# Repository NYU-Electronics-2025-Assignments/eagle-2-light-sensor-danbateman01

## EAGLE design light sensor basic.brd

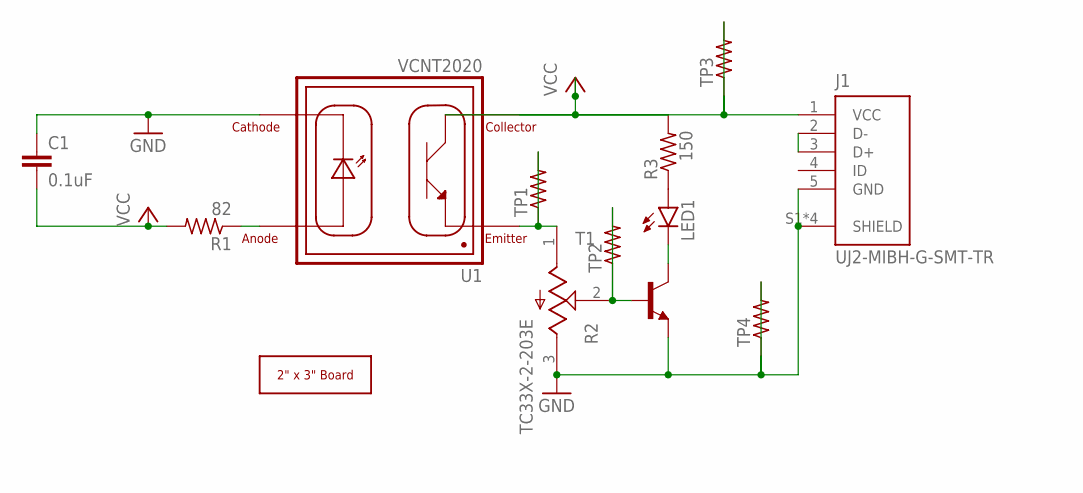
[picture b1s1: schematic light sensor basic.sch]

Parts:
C1: 0.1uF; C1206
J1: UJ2-MIBH-G-SMT-TR; CUI_UJ2-MIBH-G-SMT-TR
LED1: LEDSML0805; SML0805
R1: 82; R1206
R2: TC33X-2-203E; TRIM_TC33X-2-203E
R3: 150; R0805
T1: -NPN-SOT23-EBC; SOT23-EBC
TP1: R-US_R0805; R0805
TP2, TP3, TP4: R-US_R1206; R1206
U1: VCNT2020; XDCR_VCNT2020
U$1: 2X3_BOARD_V2

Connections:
GND: C1.1, J1.5 (GND), J1.S1 (SHIELD), J1.S2 (SHIELD), J1.S3 (SHIELD), J1.S4 (SHIELD), R2.3 (CW), T1.E, TP4.1, TP4.2, U1.4 (CATHODE)
unnamed: R1.1, U1.3 (ANODE)
unnamed: J1.2 (D-), J1.3 (D+)
unnamed: R2.2 (W), T1.B, TP2.1, TP2.2
unnamed: LED1.C, T1.C
unnamed: R2.1 (CCW), TP1.1, TP1.2, U1.1 (EMITTER)
unnamed: LED1.A, R3.1
VCC: C1.2, J1.1 (VCC), R1.2, R3.2, TP3.1, TP3.2, U1.2 (COLLECTOR)

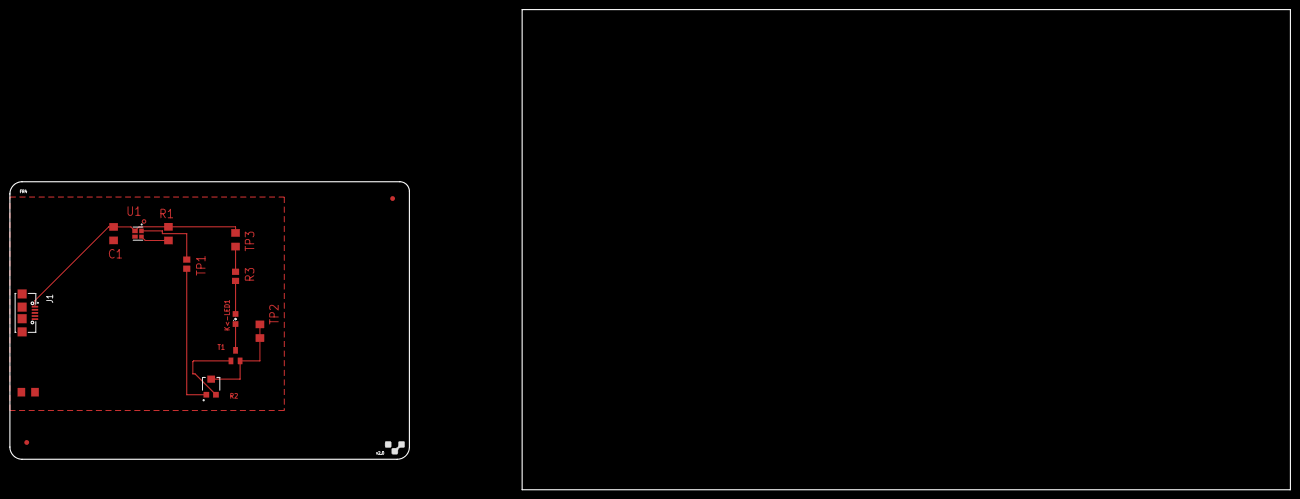
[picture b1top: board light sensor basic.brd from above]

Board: 2 copper layers, 83.2 x 57.8 mm, 13 parts (0 on the bottom side), 8 nets.

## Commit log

2025-03-01 test
2025-03-01 new test
2025-03-01 try againx2
2025-03-01 wont change
    github schematic absolutely refuses to update
2025-03-01 SHOULD WORK
